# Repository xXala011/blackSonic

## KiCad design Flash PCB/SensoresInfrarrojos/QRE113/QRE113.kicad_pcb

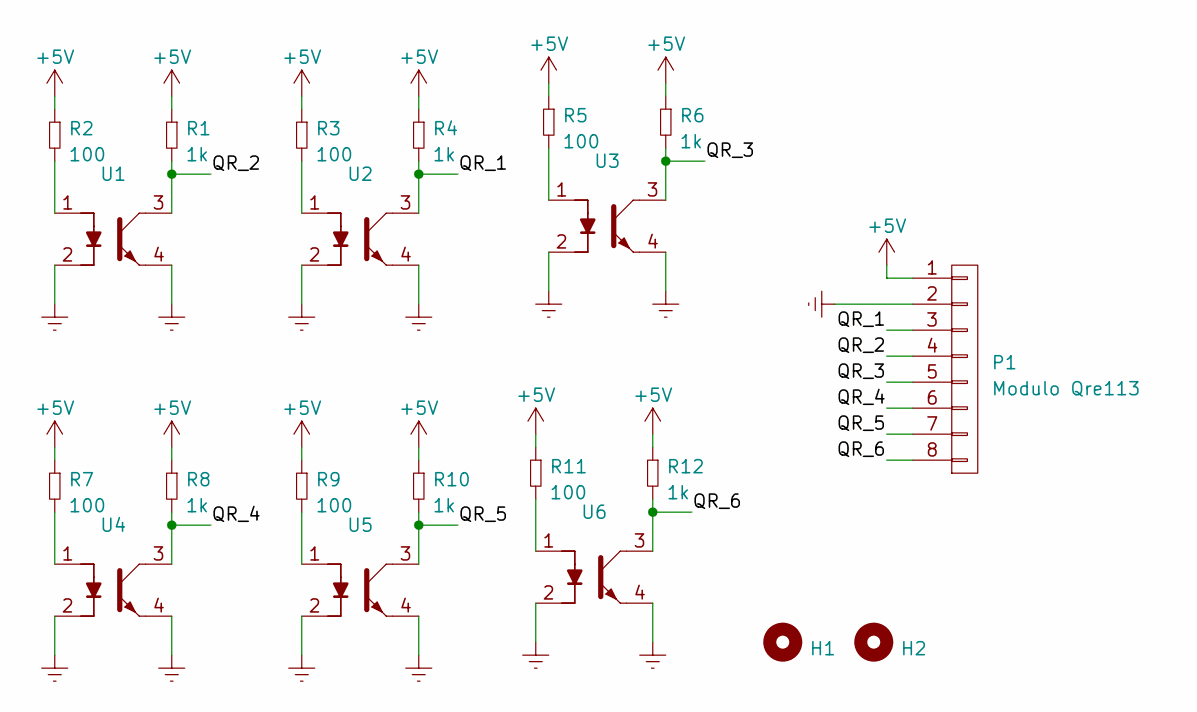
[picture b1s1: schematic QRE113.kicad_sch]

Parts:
H1, H2: Mounting_Hole; hole_3mm
P1: Modulo Qre113; Pin_Header_Straight_1x08
R1, R4, R6, R8, R10, R12: 1k; R_1206
R2, R3, R5, R7, R9, R11: 100; R_1206
U1, U2, U3, U4, U5, U6: QRE1113; QRE1113GR

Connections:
+5V: P1.1, R1.1, R2.1, R3.1, R4.1, R5.1, R6.1, R7.1, R8.1, R9.1, R10.1, R11.1, R12.1
/QR_1: P1.3, R4.2, U2.3
/QR_2: P1.4, R1.2, U1.3
/QR_3: P1.5, R6.2, U3.3
/QR_4: P1.6, R8.2, U4.3
/QR_5: P1.7, R10.2, U5.3
/QR_6: P1.8, R12.2, U6.3
Earth: P1.2, U1.2, U1.4, U2.2, U2.4, U3.2, U3.4, U4.2, U4.4, U5.2, U5.4, U6.2, U6.4
unnamed: R2.2, U1.1
unnamed: R3.2, U2.1
unnamed: R5.2, U3.1
unnamed: R7.2, U4.1
unnamed: R9.2, U5.1
unnamed: R11.2, U6.1

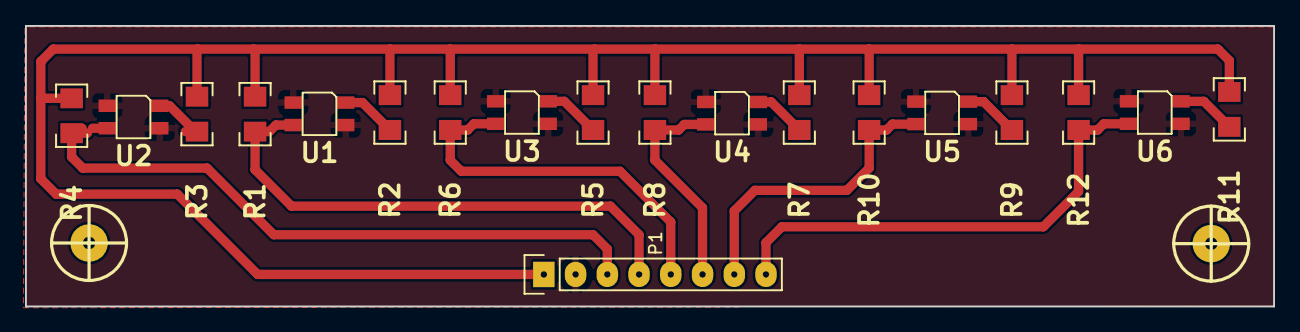
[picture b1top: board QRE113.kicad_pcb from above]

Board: 2 copper layers, 99.9 x 22.5 mm, 21 parts (0 on the bottom side), 14 nets.

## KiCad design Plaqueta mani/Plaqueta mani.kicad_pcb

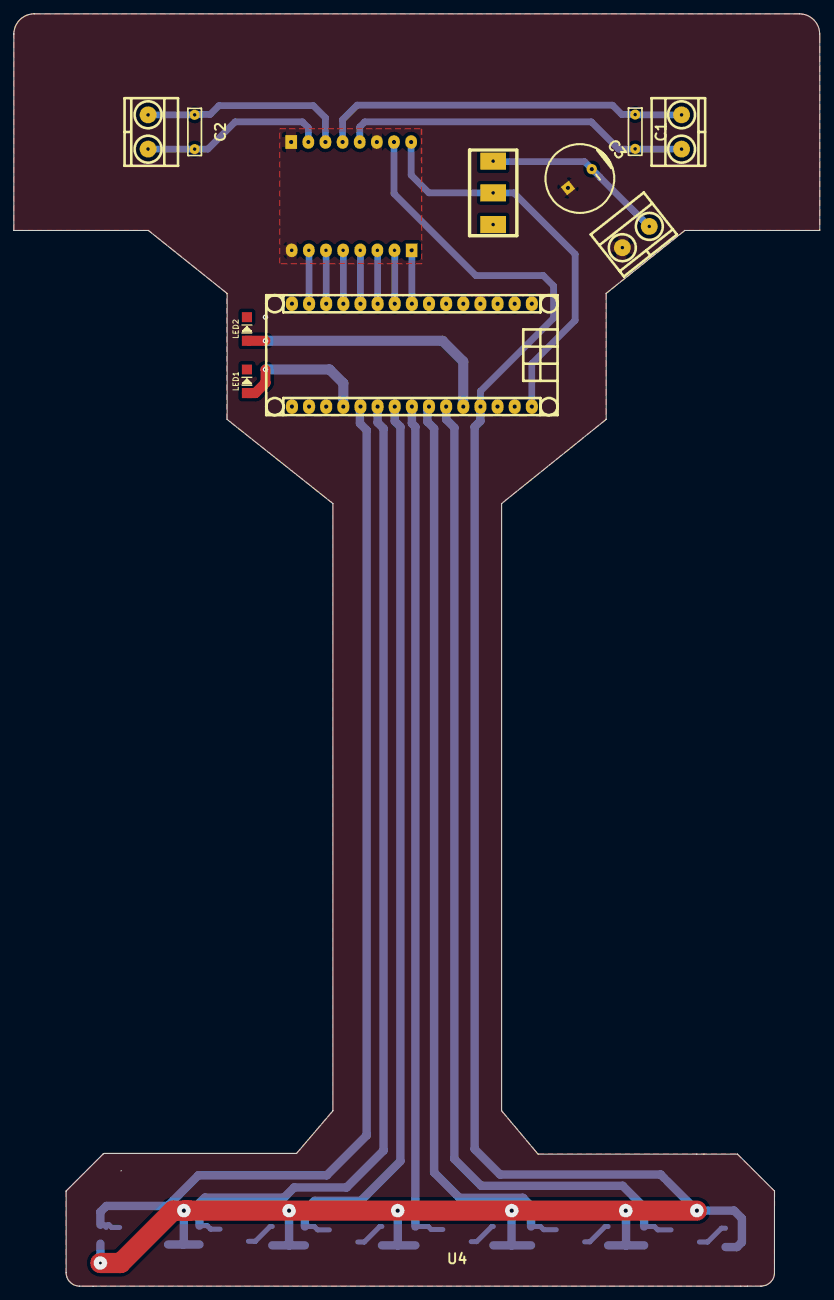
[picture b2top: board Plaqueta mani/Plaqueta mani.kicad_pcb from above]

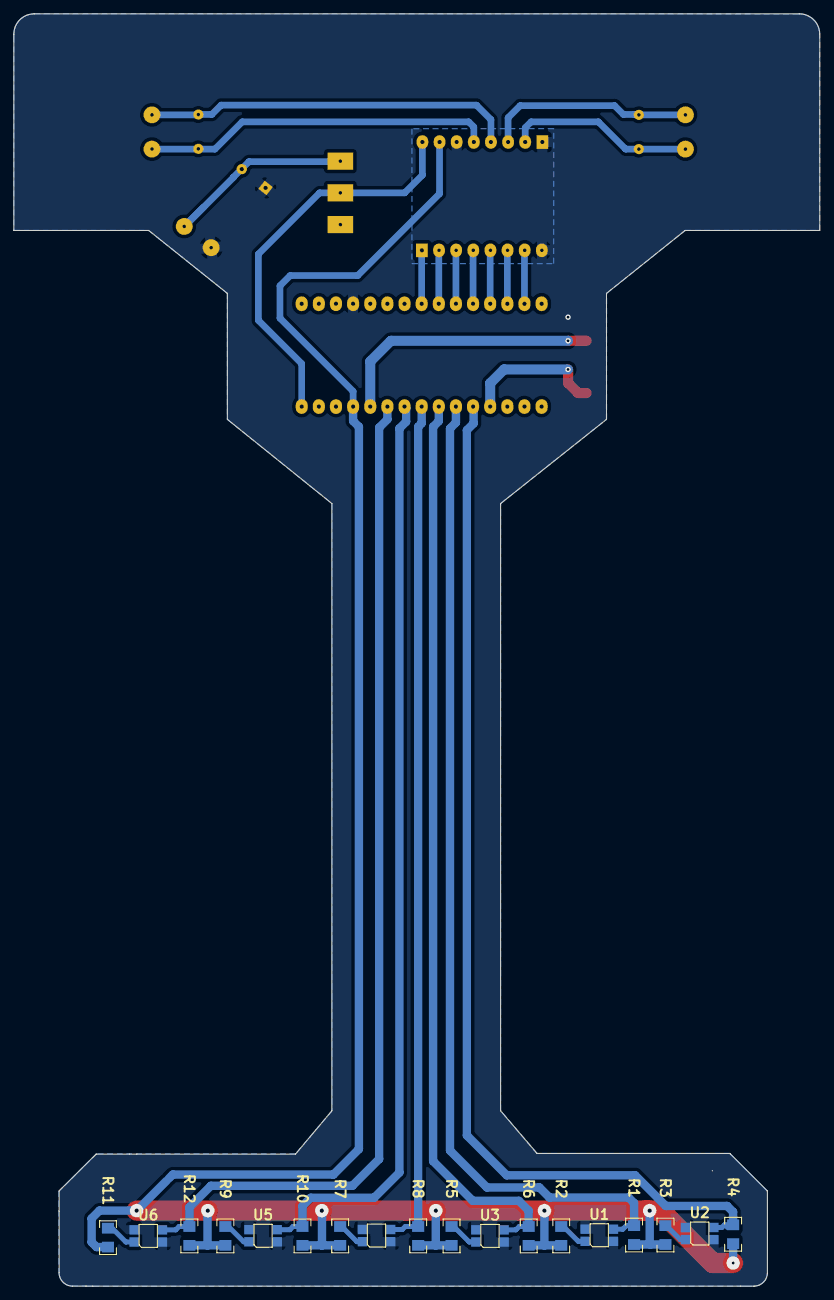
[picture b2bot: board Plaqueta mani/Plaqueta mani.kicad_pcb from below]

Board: 2 copper layers, 119.4 x 188.6 mm, 30 parts (18 on the bottom side), 23 nets.

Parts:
C1, C2: 0.1uf; CAP_0.2
C3: C; CAP_ELEC_10X8mm
J1: Arduino_Nano_Header; arduino_nano_header
J1#2, J3: HEADER_8; Pin_Header_Angled_1x08
J2: Alimentacion +7.5v; BORNERA2_AZUL
J5: Motor A; BORNERA2_AZUL
J6: Motor B; BORNERA2_AZUL
LED1, LED2: LED; LED_1206
R1, R4, R6, R8, R10, R12: 1k; R_1206
R2, R3, R5, R7, R9, R11: 100; R_1206
SW2: SW_SPDT; SW_SPDT_TH_Vertical
U1, U2, U3, U4, U5, U6: QRE1113; QRE1113GR

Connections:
+5V: J1.27 (5V), J3.7, R1.1, R2.1, R3.1, R4.1, R5.1, R6.1, R7.1, R8.1, R9.1, R10.1, R11.1, R12.1
+7.5V: J1.30 (VIN), J3.8, SW2.2 (B)
/AI1: J1.10 (D7/AIN1), J1#2.3
/AI2: J1.9 (D6/AIN0), J1#2.2
/AO1: C1.2, J3.5, J5.1
/AO2: C1.1, J3.4, J5.2
/BI1: J1.12 (D9/0C1), J1#2.5
/BI2: J1.13 (D10/SS), J1#2.6
/BO1: C2.2, J3.2, J6.2
/BO2: C2.1, J3.3, J6.1
/LED_1: J1.26 (A7), LED2.1 (A)
/LED_2: J1.19 (A0), LED1.1 (A)
/PWMA: J1.8 (D5/T1), J1#2.1
/PWMB: J1.14 (D11/MOSI), J1#2.7
/QR_1: J1.20 (A1), R4.2, U2.3
/QR_2: J1.21 (A2), R1.2, U1.3
/QR_3: J1.22 (A3), R6.2, U3.3
/QR_4: J1.23 (A4), R8.2, U4.3
/QR_5: J1.24 (A5), R10.2, U5.3
/QR_6: J1.25 (A6), R12.2, U6.3
/STBY: J1.11 (D8/ICP), J1#2.4
Earth: C3.1, J1.4 (GND), J1#2.8, J2.1, J3.1, J3.6, U1.2, U1.4, U2.2, U2.4, U3.2, U3.4, U4.2, U4.4, U5.2, U5.4, U6.2, U6.4
unnamed: C3.2, J2.2, SW2.1 (A)

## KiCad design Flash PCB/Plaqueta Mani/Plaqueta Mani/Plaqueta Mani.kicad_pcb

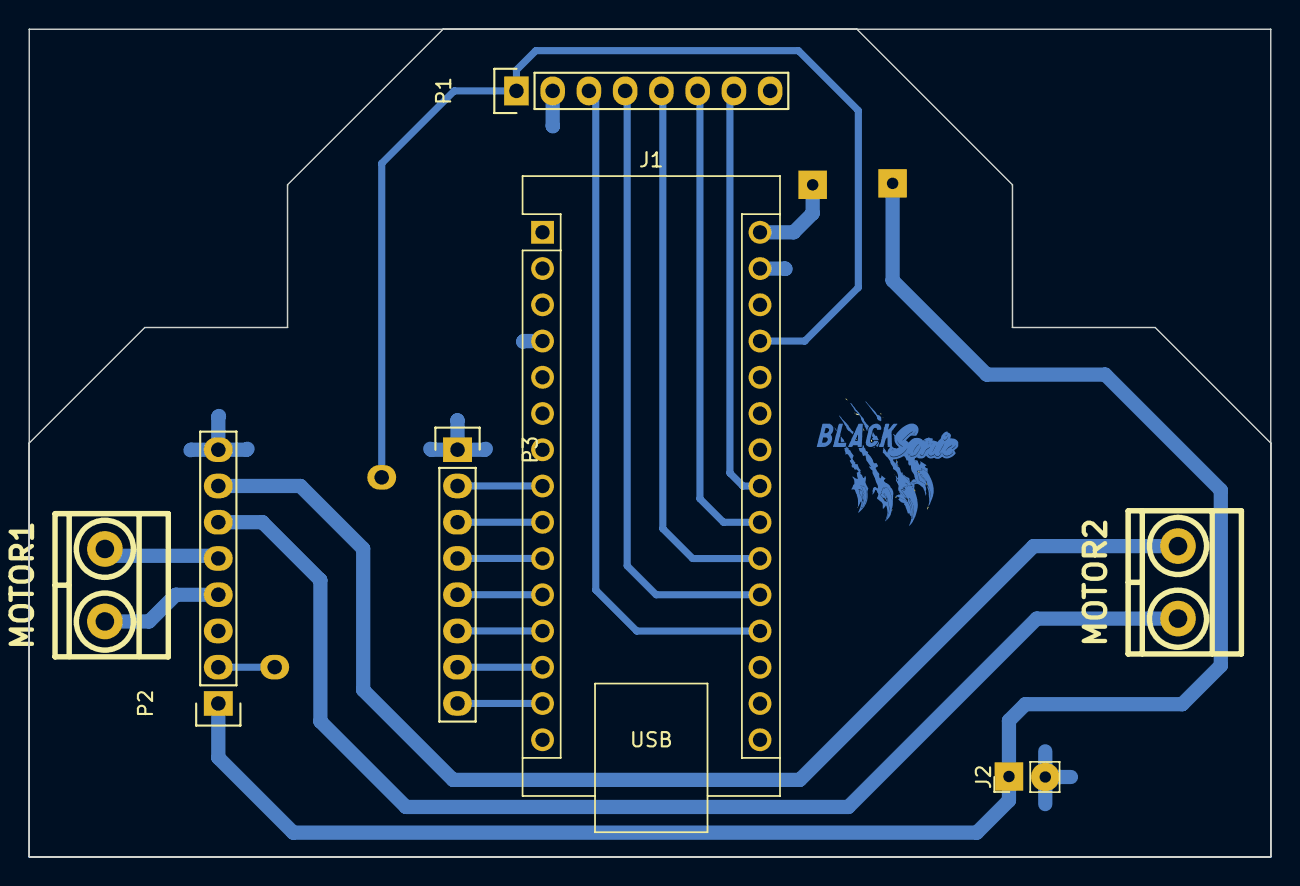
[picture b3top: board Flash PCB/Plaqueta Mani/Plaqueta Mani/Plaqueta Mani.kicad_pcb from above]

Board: 2 copper layers, 87.0 x 58.0 mm, 7 parts (0 on the bottom side), 20 nets.

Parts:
J1: Arduino_Nano_Header; Arduino_Nano
J2: VIN_BATTERY; PinHeader_1x02_P2.00mm_Vertical
J4: MOTOR1; BORNERA2_AZUL
Jr1: MOTOR2; BORNERA2_AZUL
P1: CONN_01X08; Pin_Header_Straight_1x08
P2, P3: CONN_01X08; Socket_Strip_Straight_1x08

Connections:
+5V: J1.27 (5V), P1.1, P2.2
+7.5V: J1.30 (VIN), J2.1, P2.1
/AI1: J1.12 (D9/0C1), P3.6
/AI2: J1.13 (D10/SS), P3.7
/AO1: J4.2, P2.4
/AO2: J4.1, P2.5
/BI1: J1.10 (D7/AIN1), P3.4
/BI2: J1.9 (D6/AIN0), P3.3
/BO1: Jr1.1, P2.7
/BO2: Jr1.2, P2.6
/PWMA: J1.14 (D11/MOSI), P3.8
/PWMB: J1.8 (D5/T1), P3.2
/QR_1: J1.19 (A0), P1.3
/QR_2: J1.20 (A1), P1.4
/QR_3: J1.21 (A2), P1.5
/QR_4: J1.22 (A3), P1.6
/QR_5: J1.23 (A4), P1.7
/QR_6: J1.24 (A5), P1.8
/STBY: J1.11 (D8/ICP), P3.5
Earth: J1.4 (GND), J1.29 (GND), J2.2, P1.2, P2.3, P2.8, P3.1

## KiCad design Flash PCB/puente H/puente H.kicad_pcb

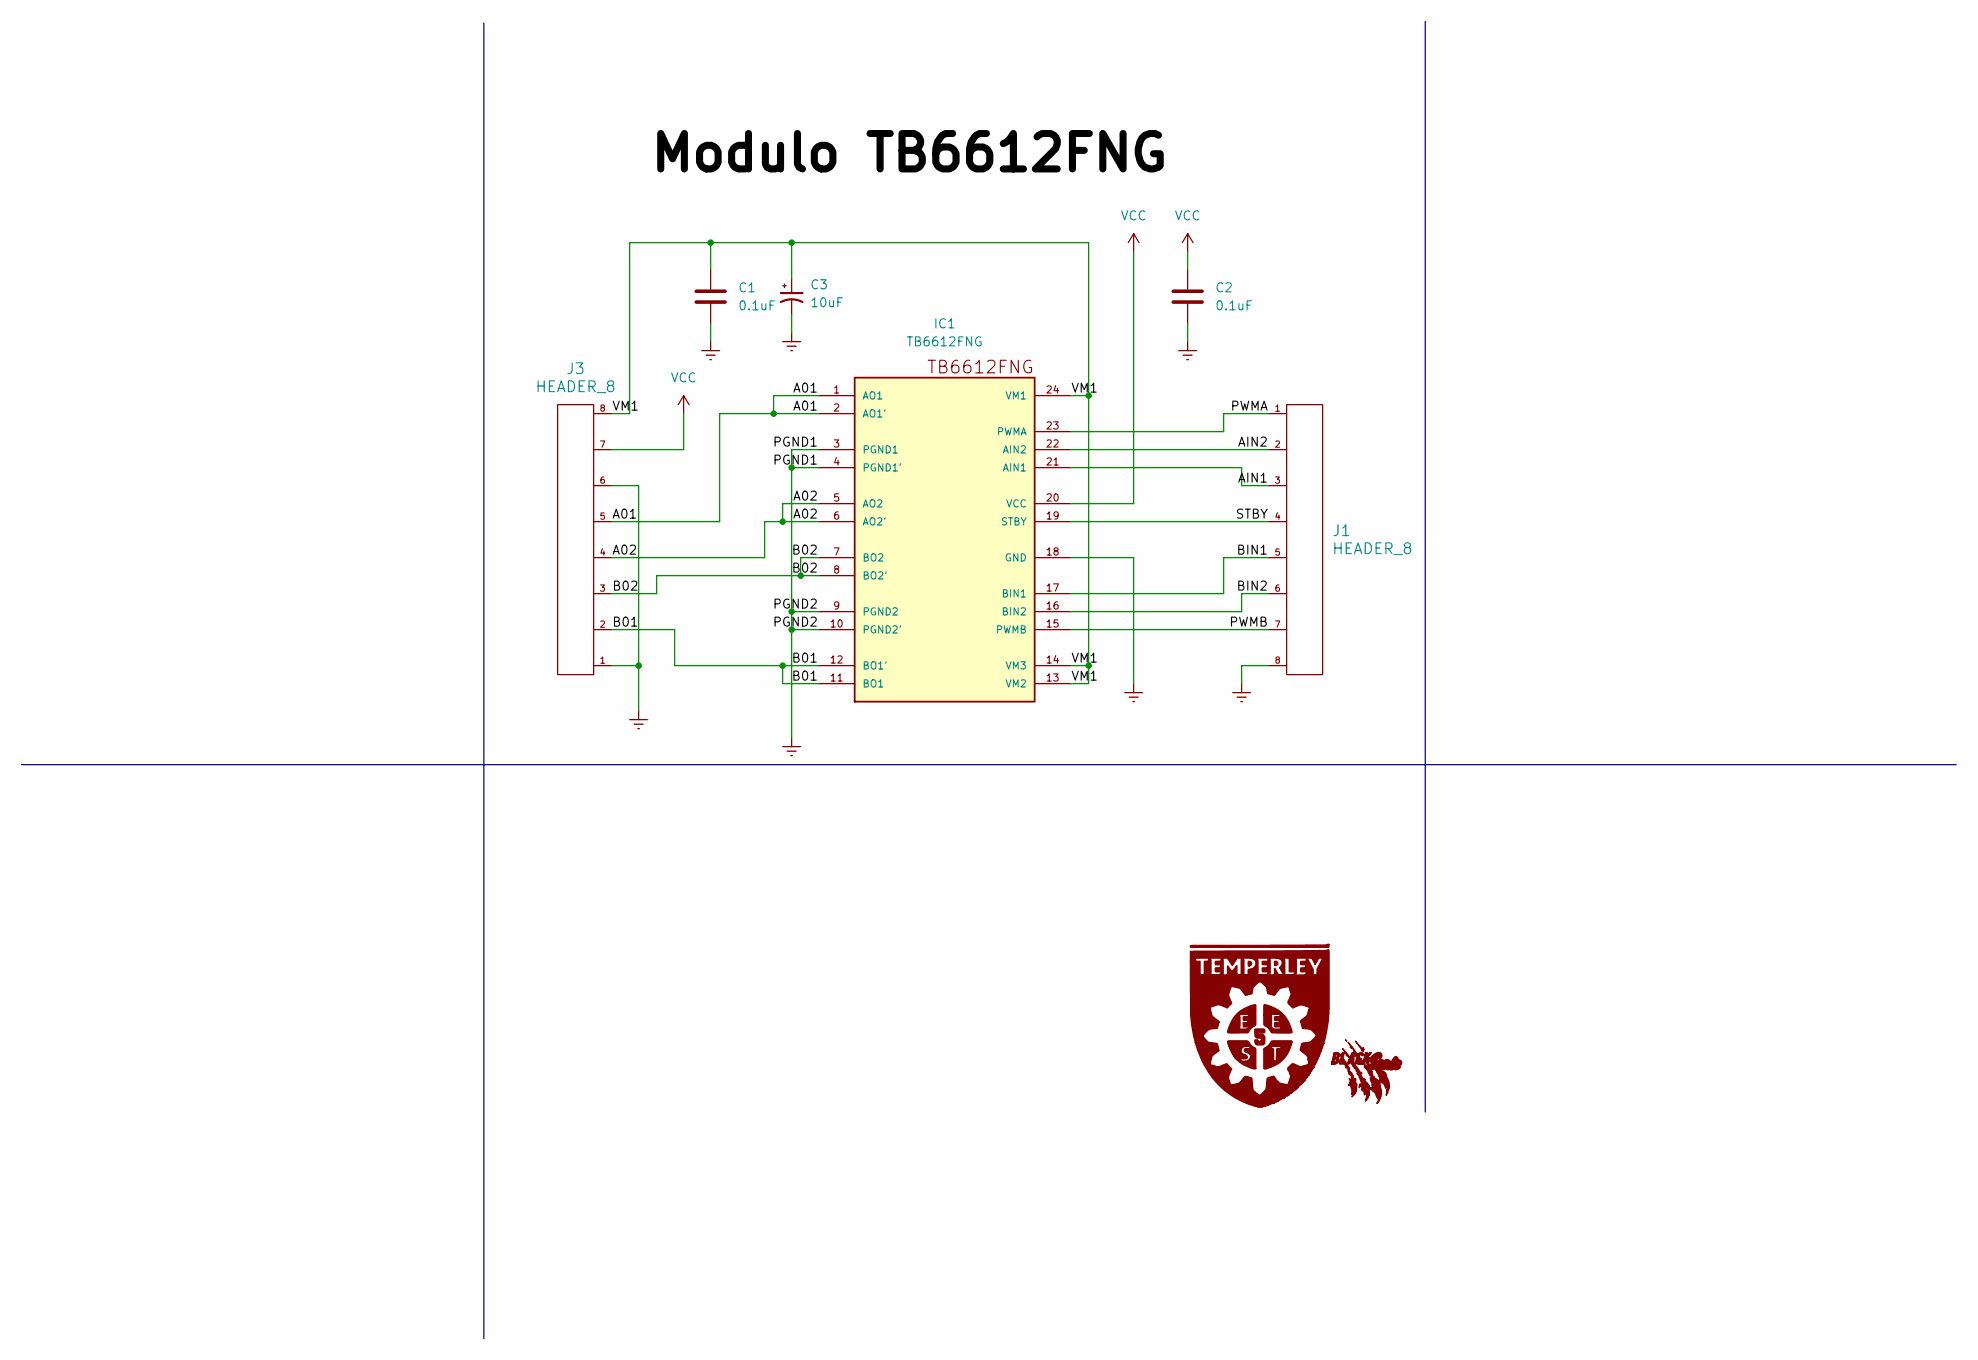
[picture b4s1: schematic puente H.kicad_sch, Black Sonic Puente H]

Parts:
C1, C2: 0.1uF; C_0504_1310Metric_Pad0.83x1.28mm_HandSolder
C3: 10uF; CP_EIA-3528-21_Kemet-B_Pad1.50x2.35mm_HandSolder
IC1: TB6612FNG; SSOP24
J1, J3: HEADER_8; Pin_Header_Angled_1x08

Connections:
/A01: IC1.1 (AO1), IC1.2 (AO1'), J3.5
/A02: IC1.5 (AO2), IC1.6 (AO2'), J3.4
/AIN1: IC1.21 (AIN1), J1.3
/AIN2: IC1.22 (AIN2), J1.2
/B01: IC1.11 (BO1), IC1.12 (BO1'), J3.2
/B02: IC1.7 (BO2), IC1.8 (BO2'), J3.3
/BIN1: IC1.17 (BIN1), J1.5
/BIN2: IC1.16 (BIN2), J1.6
/PWMA: IC1.23 (PWMA), J1.1
/PWMB: IC1.15 (PWMB), J1.7
/STBY: IC1.19 (STBY), J1.4
/VM1: C1.1, C3.1, IC1.13 (VM2), IC1.14 (VM3), IC1.24 (VM1), J3.8
Earth: C1.2, C2.2, C3.2, IC1.3 (PGND1), IC1.4 (PGND1'), IC1.9 (PGND2), IC1.10 (PGND2'), IC1.18 (GND), J1.8, J3.1, J3.6
VCC: C2.1, IC1.20 (VCC), J3.7

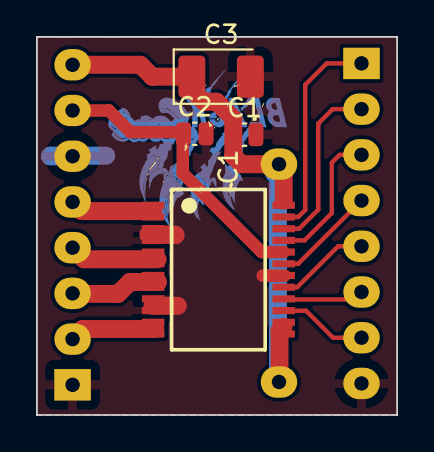
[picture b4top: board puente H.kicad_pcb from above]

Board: 2 copper layers, 20.0 x 21.0 mm, 6 parts (0 on the bottom side), 14 nets.

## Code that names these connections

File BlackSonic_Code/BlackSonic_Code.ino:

#include <QTRSensors.h>
QTRSensors qtr;

#define Calibration_Time   2000  

#define LED1          21
#define LED2          14

#define STBY          8

//Para el motor A
#define PWMA          5
#define AIN1          7
#define AIN2          6

//Para el motor B
#define PWMB          11
#define BIN1          9
#define BIN2          10

const uint8_t Number_Sensors = 6;     //numero de sensores usados
uint16_t sensorValues[Number_Sensors];

//Variables para el PID
float Kp=0;
float Kd=0;
float Ki=0;

unsigned long TiempoAhora = 0;

int periodo = 250;                    
int velocidad=135;

int Proporcional=0;
int derivativo=0;
int integral=0;
int salida_pwm=0;
int proporcional_pasado=0;
int position=0;
int position_print=0;

int motor_adelante=0;
int motor_atras=0;


void Adelante(){
  digitalWrite(STBY, LOW);
  analogWrite(PWMA, 135);
  analogWrite(PWMB, 135);
  digitalWrite(AIN1, HIGH);
  digitalWrite(BIN1, HIGH);
  digitalWrite(BIN2, LOW);
}

void Atras(){
  digitalWrite(STBY, LOW);
  analogWrite(PWMA, 135);
  analogWrite(PWMB, 135);
  digitalWrite(AIN2, HIGH);
  digitalWrite(AIN1, LOW);
  digitalWrite(BIN1, LOW);
  digitalWrite(BIN2, HIGH);
}

void Izquierda(){
  digitalWrite(STBY, LOW);
  analogWrite(PWMA, motor_atras);
  analogWrite(PWMB, motor_adelante);
  digitalWrite(AIN2, LOW);
  digitalWrite(AIN1, LOW);
  digitalWrite(BIN1, HIGH);
  digitalWrite(BIN2, LOW);
}

void Derecha(){
  digitalWrite(STBY, LOW);
  analogWrite(PWMA, motor_adelante);
  analogWrite(PWMB, motor_atras);
  digitalWrite(AIN2, LOW);
  digitalWrite(AIN1, HIGH);
  digitalWrite(BIN1, HIGH);
  digitalWrite(BIN2, LOW);
}

void Stop(){
  digitalWrite(STBY,  HIGH);
  digitalWrite(AIN2, LOW);
  digitalWrite(AIN1, LOW);
  digitalWrite(BIN1, LOW);
  digitalWrite(BIN2, LOW);
}

void pid(int velocidad, float Kp, float Ki, float Kd){

  uint16_t position = qtr.readLineBlack(sensorValues);

  Proporcional = (position) - 2500;

  if (Proporcional<0){
    Izquierda();
  }

  else if (Proporcional>0){
    Derecha();
  }

  integral += Proporcional;

  derivativo = (Proporcional - proporcional_pasado);

  if (integral>1000) integral=1000;
  if (integral<-1000) integral=-1000;

   salida_pwm = ( Proporcional * Kp ) + ( derivativo * Kd ) + (integral * Ki);

  if (  salida_pwm > velocidad )  salida_pwm = velocidad; 
  if ( salida_pwm < -velocidad )  salida_pwm = -velocidad;

  motor_adelante = (salida_pwm + velocidad);
  motor_atras = (salida_pwm - velocidad);

  if (motor_adelante > 255) motor_adelante = 255;
  if (motor_atras < 0) motor_atras = 0;

  proporcional_pasado = Proporcional;

}

void setup() {

  pinMode(STBY, OUTPUT);  
  pinMode(PWMA, OUTPUT);
  pinMode(AIN1, OUTPUT);
  pinMode(AIN2, OUTPUT);
  pinMode(PWMB, OUTPUT);
  pinMode(BIN1, OUTPUT);
  pinMode(BIN2, OUTPUT);

  pinMode(LED1, OUTPUT);
  pinMode(LED2, OUTPUT);

  qtr.setTypeAnalog();
  qtr.setSensorPins((const uint8_t[]){A1, A2, A3, A4, A5, A6}, Number_Sensors);

  delay(500);

  //Se prende el led1 indicando la etapa de calibracion.
  digitalWrite(LED1, HIGH);

   for (uint16_t i = 0; i < 400; i++)
  {
    qtr.calibrate();
  }

  digitalWrite(LED1, LOW);
  //Se apaga el led 1 y se prende el led2 indicando que ya termino la etapa de calibracion.
  digitalWrite(LED2, HIGH);

}

void loop() {

analogWrite(PWMA, velocidad);
analogWrite(PWMB, velocidad);

  for (uint8_t i = 0; i < Number_Sensors; i++)
  {
    Serial.print(sensorValues[i]);
    Serial.print('\t');
  }
  if(millis() > TiempoAhora + periodo)
  {
    TiempoAhora = millis();
    position_print = qtr.readLineBlack(sensorValues);
    Serial.println(position_print);
  }

  pid(velocidad,Kp,Ki,Kd);

}

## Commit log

2023-08-23 Abriendo el repositorio
2023-08-23 Infrarrojos PCB v0.1
2023-08-23 COrrijiendo ramas
2023-08-23 Yes
    afafsff
2023-08-23 Hardware
2023-08-25 Borrando y reacomodando archivos
2023-08-25 Arreglando Error
2023-08-25 Arreglando errores de diseño
2023-08-25 Arreglando Puente H
2023-08-30 Agregue la plaqueta main del velocista v0.1
2023-09-01 PLaqueta Mani Milton
2023-09-26 Agregue leds y actualice los pads del plaqueta mani
2023-10-20 Agregue el codigo de blacksonic 1.0
    Falta testear, por lo tanto los valores son experimentales..
2024-02-04 Soporte Rueda v1.1
2024-02-04 Soporte Mbappe v1.01
2024-02-07 Soporte Mbappe v2
2024-02-17 Codigo principal BlackSonic v1
2024-02-18 adasdasdasd
2024-04-26 Informe final - Proyecto Concluido
